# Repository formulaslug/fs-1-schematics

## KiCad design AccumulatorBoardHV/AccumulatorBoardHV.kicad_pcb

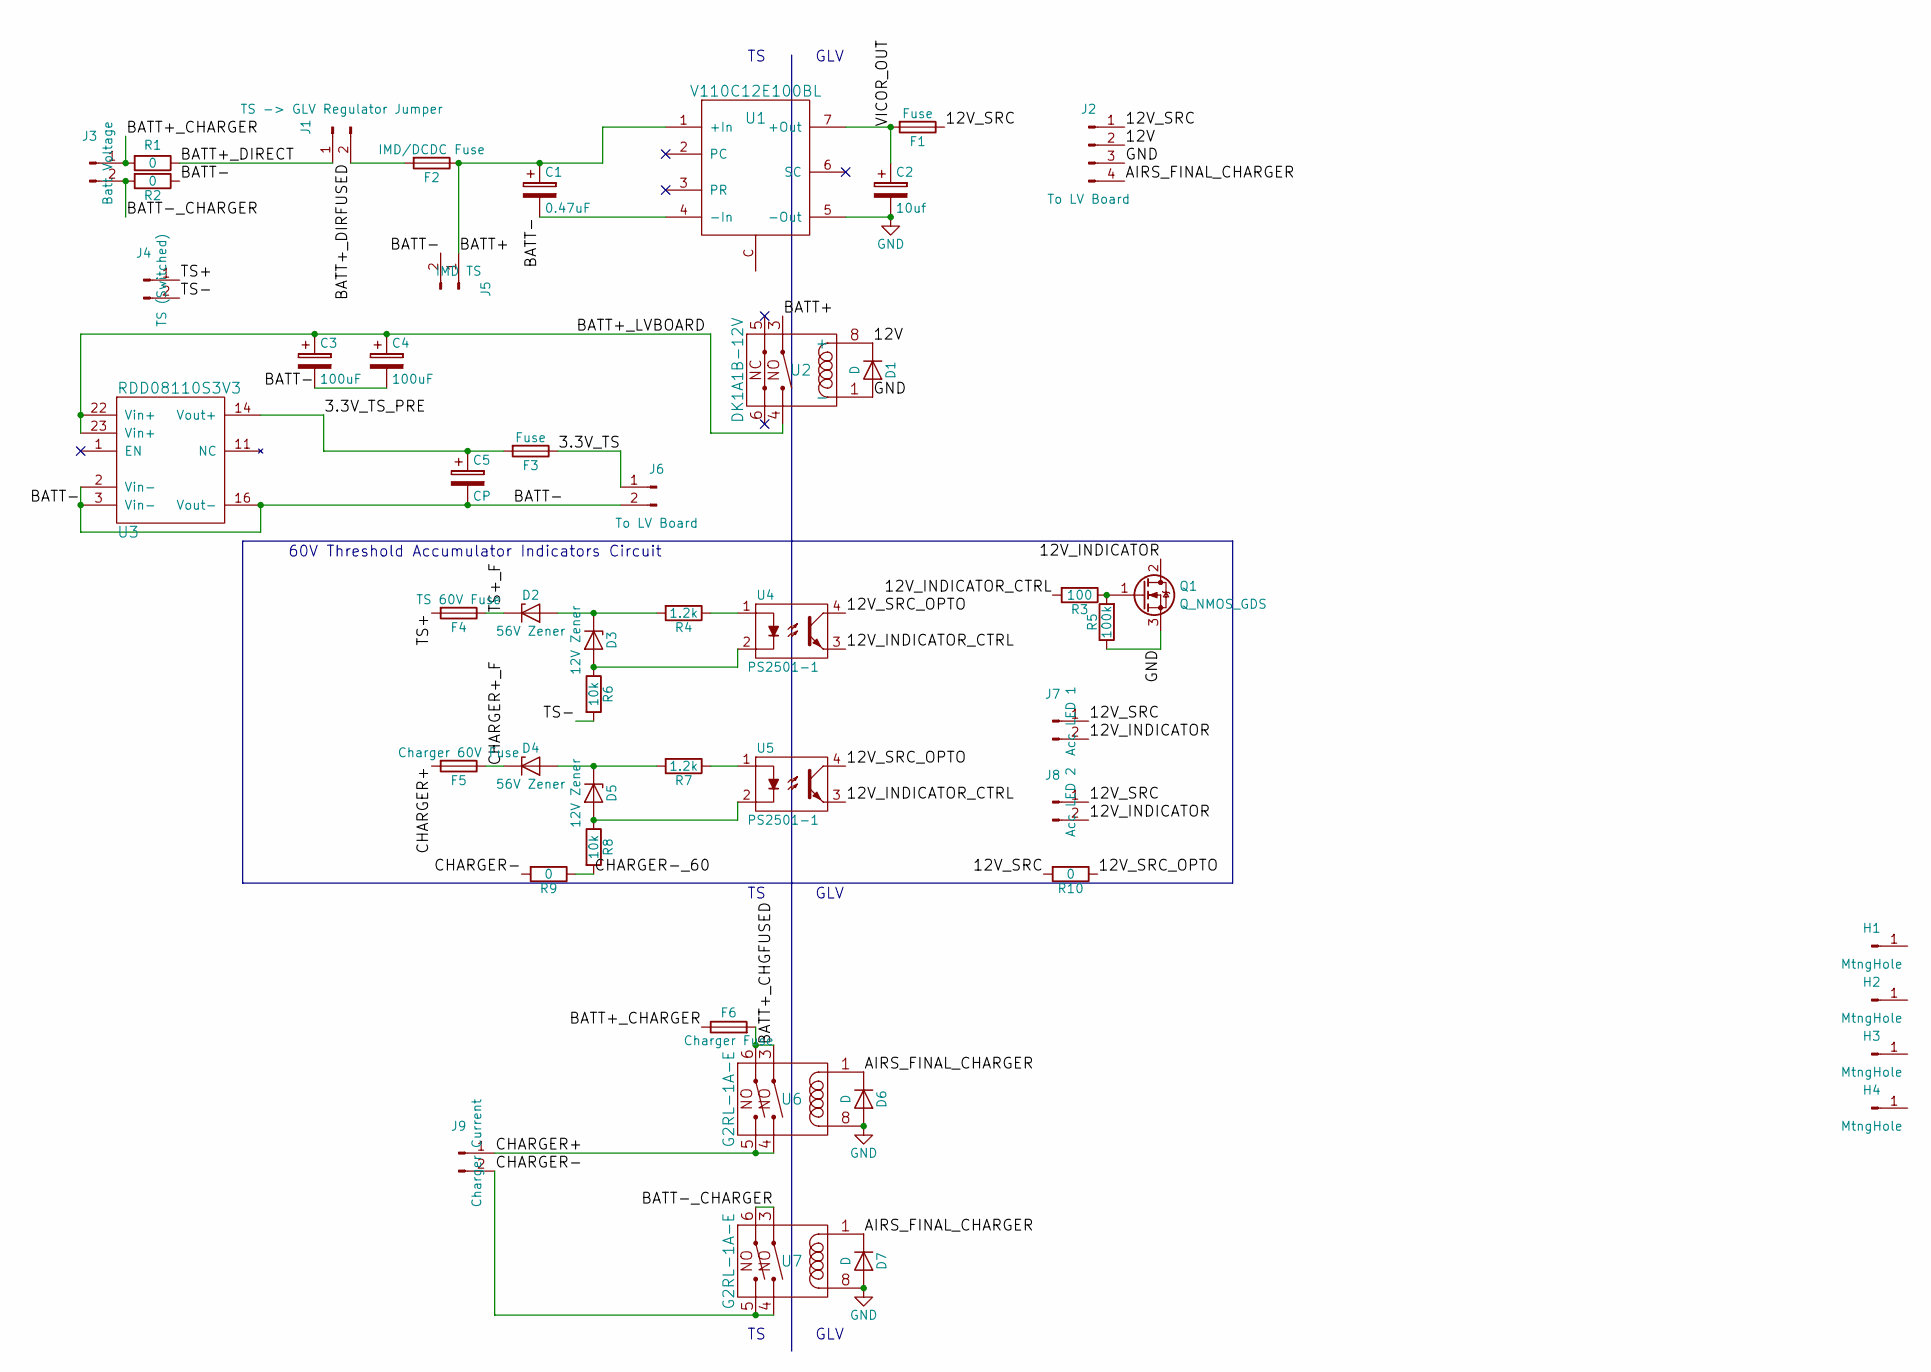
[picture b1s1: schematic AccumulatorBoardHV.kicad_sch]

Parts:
C1: 0.47uF; CP_Radial_D8.0mm_P2.50mm
C2: 10uf; CP_Radial_D8.0mm_P2.50mm
C3, C4: 100uF; CP_Radial_D16.0mm_P7.50mm
C5: CP; CP_Radial_D8.0mm_P2.50mm
D1, D6, D7: D; D_1206
D2, D4: 56V Zener; D_A-405_P7.62mm_Horizontal
D3, D5: 12V Zener; D_A-405_P7.62mm_Horizontal
F1, F3: Fuse; SMD Fuse
F2: IMD/DCDC Fuse; Fuseholder5x20_vert
F4: TS 60V Fuse; SMD Fuse
F5: Charger 60V Fuse; SMD Fuse
F6: Charger Fuse; Fuseholder5x20_vert
H1, H2, H3, H4: MtngHole; MountingHole_4.5mm
J1: TS -> GLV Regulator Jumper; Molex_NanoFit_1x02x2.50mm_Straight
J2: To LV Board; Molex_NanoFit_2x02x2.50mm_Straight
J3: Batt Voltage; Molex_MiniFit-JR-5556-02A_2x01x4.20mm_Straight
J4: TS (Switched); Molex_NanoFit_1x02x2.50mm_Straight
J5: IMD TS; Molex_NanoFit_1x02x2.50mm_Straight
J6: To LV Board; Molex_NanoFit_1x02x2.50mm_Straight
J7: Acc LED 1; Molex_NanoFit_1x02x2.50mm_Straight
J8: Acc LED 2; Molex_NanoFit_1x02x2.50mm_Straight
J9: Charger Current; Molex_MiniFit-JR-5556-02A_2x01x4.20mm_Straight
Q1: Q_NMOS_GDS; TO-220-3_Vertical
R1, R2, R9, R10: 0; SMDNetTie
R3: 100; R_Axial_DIN0207_L6.3mm_D2.5mm_P10.16mm_Horizontal
R4, R7: 1.2k; R_Axial_DIN0207_L6.3mm_D2.5mm_P10.16mm_Horizontal
R5: 100k; R_Axial_DIN0207_L6.3mm_D2.5mm_P10.16mm_Horizontal
R6, R8: 10k; R_Axial_DIN0411_L9.9mm_D3.6mm_P12.70mm_Horizontal
U1: V110C12E100BL; Vicor_Micro
U2: DK1A1B-12V
U3: RDD08110S3V3
U4, U5: PS2501-1; DIP-4_W7.62mm
U6, U7: G2RL-1A-E

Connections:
/3.3V_TS: F3.1, J6.1
/3.3V_TS_PRE: C5.1, F3.2, U3.14 (Vout+)
/12V: D1.1 (K), J2.2, U2.8 (+)
/12V_INDICATOR: J7.2, J8.2, Q1.2 (D)
/12V_INDICATOR_CTRL: R3.2, U4.3, U5.3
/12V_SRC: F1.1, J2.1, J7.1, J8.1, R10.2
/12V_SRC_OPTO: R10.1, U4.4, U5.4
/AIRS_FINAL_CHARGER: D6.1 (K), D7.1 (K), J2.4, U6.1, U7.1
/BATT+: C1.1, F2.1, J5.1, U1.1 (+In), U2.3
/BATT+_CHARGER: F6.1, J3.1, R1.2
/BATT+_CHGFUSED: F6.2, U6.3, U6.6
/BATT+_DIRECT: J1.1, R1.1
/BATT+_DIRFUSED: F2.2, J1.2
/BATT+_LVBOARD: C3.1, C4.1, U2.4, U3.22 (Vin+), U3.23 (Vin+)
/BATT-: C1.2, C3.2, C4.2, C5.2, J5.2, J6.2, R2.1, U1.4 (-In), U3.2 (Vin-), U3.3 (Vin-), U3.16 (Vout-)
/BATT-_CHARGER: J3.2, R2.2, U7.3, U7.6
/CHARGER+: F5.2, J9.1, U6.4, U6.5
/CHARGER+_F: D4.1 (K), F5.1
/CHARGER-: J9.2, R9.2, U7.4, U7.5
/CHARGER-_60: R8.2, R9.1
/TS+: F4.2, J4.1
/TS+_F: D2.1 (K), F4.1
/TS-: J4.2, R6.2
/VICOR_OUT: C2.1, F1.2, U1.7 (+Out)
GND: C2.2, D1.2 (A), D6.2 (A), D7.2 (A), J2.3, Q1.3 (S), R5.1, U1.5 (-Out), U2.1 (-), U6.8, U7.8
unnamed: D2.2 (A), D3.1 (K), R4.2
unnamed: D3.2 (A), R6.1, U4.2
unnamed: D4.2 (A), D5.1 (K), R7.2
unnamed: D5.2 (A), R8.1, U5.2
unnamed: Q1.1 (G), R3.1, R5.2
unnamed: R4.1, U4.1
unnamed: R7.1, U5.1

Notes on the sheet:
TS GLV
60V Threshold Accumulator Indicators Circuit

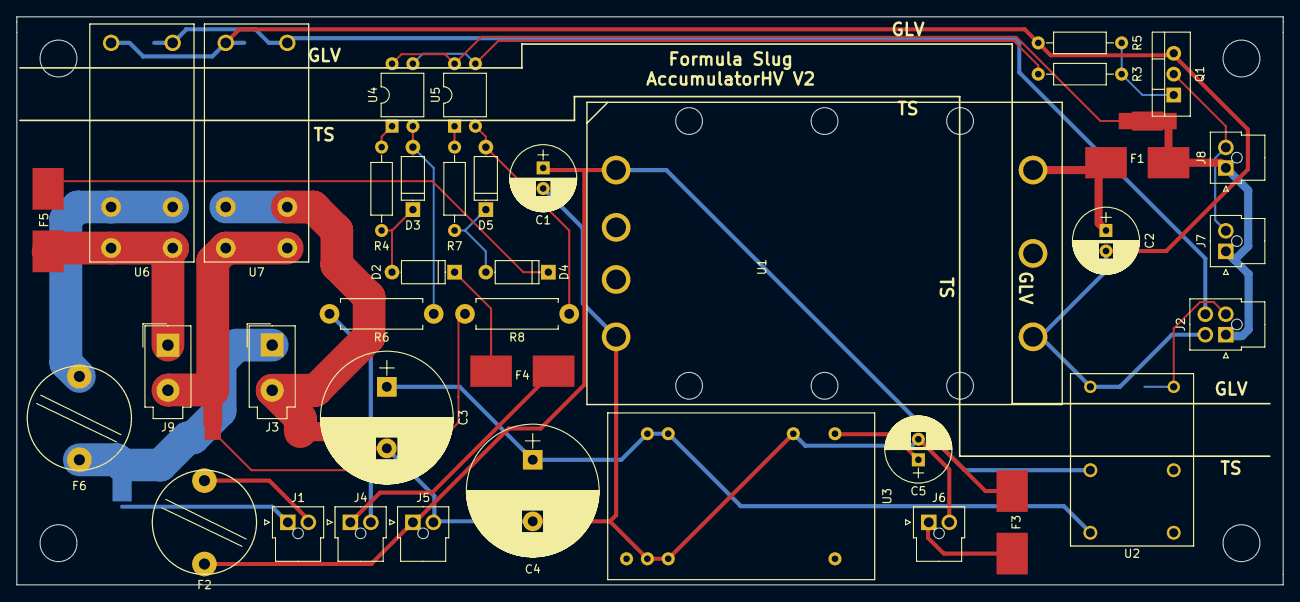
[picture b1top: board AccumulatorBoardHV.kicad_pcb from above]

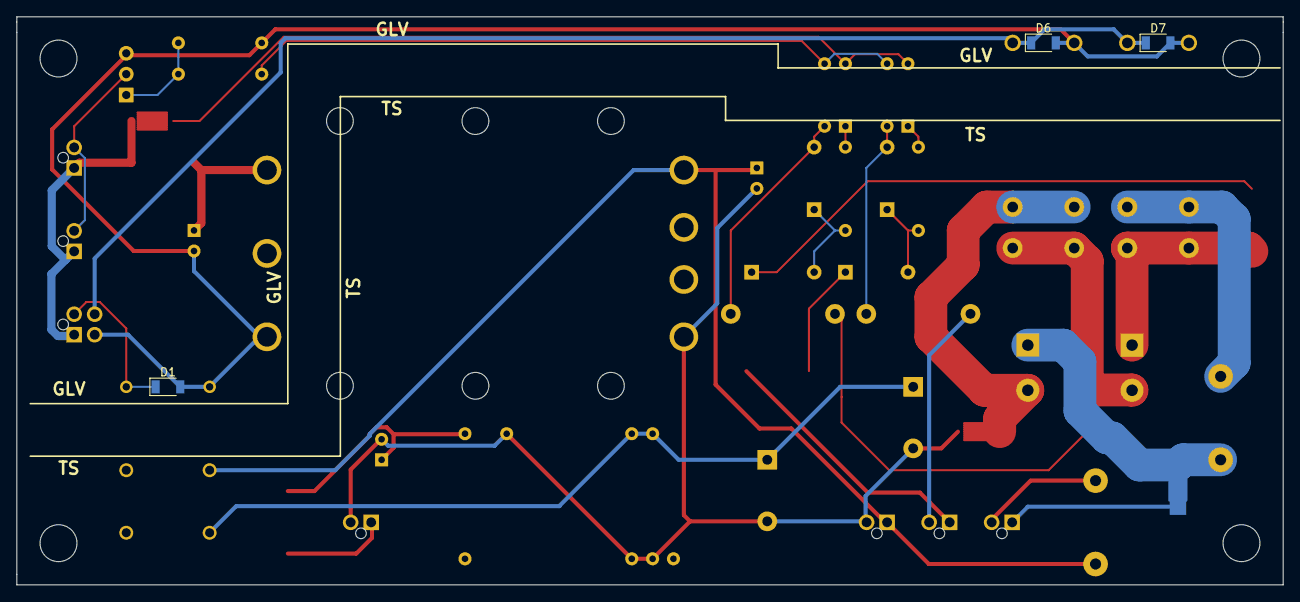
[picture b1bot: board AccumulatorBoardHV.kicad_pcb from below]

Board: 2 copper layers, 154.3 x 69.2 mm, 49 parts (4 on the bottom side), 32 nets.

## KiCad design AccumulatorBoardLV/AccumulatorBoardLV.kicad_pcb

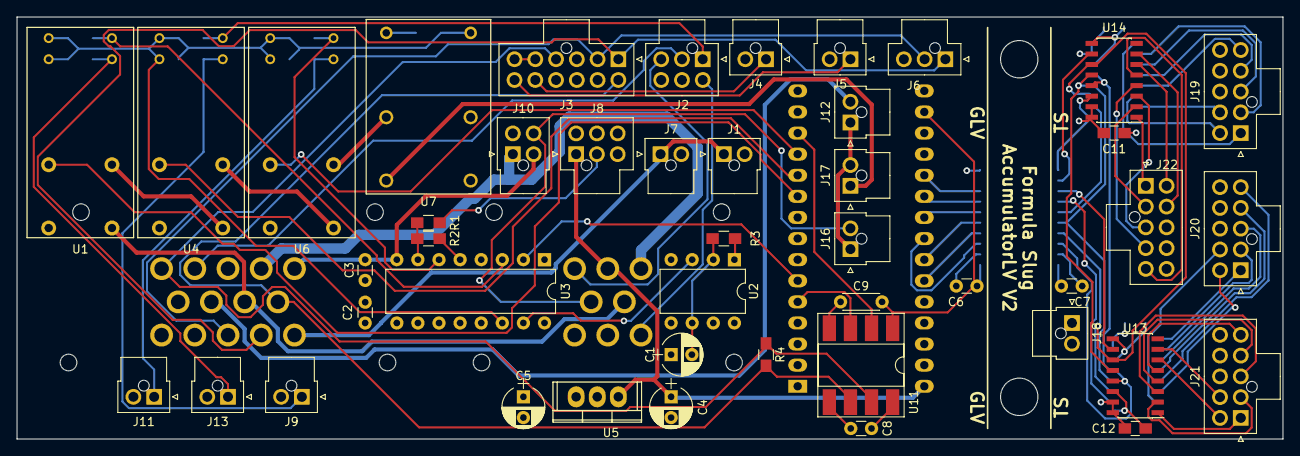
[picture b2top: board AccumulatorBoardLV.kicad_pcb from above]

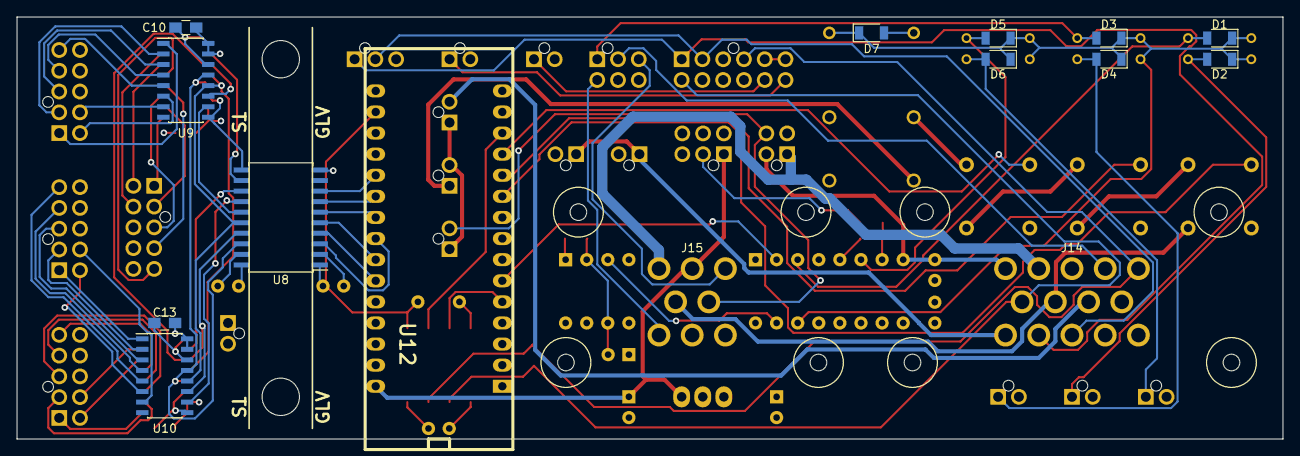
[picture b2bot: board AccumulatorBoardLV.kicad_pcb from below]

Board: 4 copper layers, 152.4 x 50.8 mm, 62 parts (15 on the bottom side), 84 nets.

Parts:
C1, C4, C5: 10uF; CP_Radial_D5.0mm_P2.50mm
C2, C3, C6, C7: 0.1uF; C_Disc_D3.0mm_W1.6mm_P2.50mm
C8: CP; C_Disc_D3.0mm_W1.6mm_P2.50mm
C9: CP; C_Disc_D4.3mm_W1.9mm_P5.00mm
C10, C11, C12, C13: 1uF; C_0805_HandSoldering
D1, D2, D3, D4, D5, D6, D7: D; D_1206
H1, H2: MtngHole; MountingHole_4.5mm
J1: Contactor 1; Molex_NanoFit_1x02x2.50mm_Straight
J2: BMS Connector 1; Molex_NanoFit_2x03x2.50mm_Straight
J3: BMS Connector 2; Molex_NanoFit_2x06x2.50mm_Straight
J4: BMS TX; Molex_NanoFit_1x02x2.50mm_Straight
J5: BMS RX; Molex_NanoFit_1x02x2.50mm_Straight
J6: Current Sensor; Molex_NanoFit_1x03x2.50mm_Straight
J7: Contactor 2; Molex_NanoFit_1x02x2.50mm_Straight
J8: IMD LV; Molex_NanoFit_2x03x2.50mm_Straight
J9: BMS Reset; Molex_NanoFit_1x02x2.50mm_Straight
J10: To HV Board; Molex_NanoFit_2x02x2.50mm_Straight
J11: IMD Reset; Molex_NanoFit_1x02x2.50mm_Straight
J12: TS Interlock; Molex_NanoFit_1x02x2.50mm_Straight
J13: Temp Reset; Molex_NanoFit_1x02x2.50mm_Straight
J14: To ECU; Ampseal-776261
J15: Charger LV; Ampseal-776276-1
J16: Charger Interlock; Molex_NanoFit_1x02x2.50mm_Straight
J17: Lid Interlock; Molex_NanoFit_1x02x2.50mm_Straight
J18: From HV Board; Molex_NanoFit_1x02x2.50mm_Straight
J19: Chip 1; Molex_NanoFit_2x05x2.50mm_Straight
J20: Chip 2; Molex_NanoFit_2x05x2.50mm_Straight
J21: Chip 3; Molex_NanoFit_2x05x2.50mm_Straight
J22: Chip 4; Molex_NanoFit_2x05x2.50mm_Straight
R1, R2: 1.1kR; R_0805_HandSoldering
R3: 470kR; R_0805_HandSoldering
R4: 120; R_0805_HandSoldering
U1, U4, U6: DE1A1B-L2-12V
U2: LM555N; DIP-8_W7.62mm
U3: SN754410; DIP-16_W7.62mm
U5: L78S05CV-DG; TO-220
U7: DK1A1B-12V
U8: ADUM4154ARIZ; SOIC-20W_7.5x12.8mm_Pitch1.27mm
U9, U10, U13, U14: MCP3008; SOIC-16_3.9x9.9mm_Pitch1.27mm
U11: ISO1050; DIP-8_W8.89mm_SMDSocket_LongPads
U12: stm_nucleo_FK303K8; arduino_mini

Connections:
+3V3: C6.1, C9.1, U8.1, U11.1, U12.17
+5V: C1.1, C2.1, C5.1, C8.1, U2.4, U2.8, U3.1, U3.9, U3.16, U5.3, U11.8
+12V: C3.1, C4.1, J8.1, J10.2, J14.1, J15.2, U3.8, U5.1, U12.30
/3.3V_TS: C7.1, C10.1, C11.1, C12.1, C13.1, J18.1, J19.9, J20.9, J21.9, J22.9, U8.20, U9.15, U9.16, U10.15, U10.16, U13.15, U13.16, U14.15, U14.16
/5V_BMS: J3.1, J6.1, J14.11
/12V_SRC: J10.1, J14.2, J15.1
/AIRS_ACC_OUT: J12.2, J14.8
/AIRS_BMS_OUT: U4.6, U6.5
/AIRS_CHARGER_OUT: J14.7, J15.4, U1.5
/AIRS_FINAL: J1.1, J7.1, J14.10
/AIRS_FINAL_CHARGER: J10.4, J15.5, J16.2
/AIRS_IMD_OUT: U6.6, U7.3
/AIRS_LID_OUT: J12.1, J16.1, J17.2
/AIRS_RELAYS_OUT: J17.1, U7.4
/AIRS_TEMP_OUT: U1.6, U4.5
/BATT-: C7.2, C10.2, C11.2, C12.2, C13.2, J18.2, J19.10, J20.10, J21.10, J22.10, U8.11, U8.19, U9.9, U9.14, U10.9, U10.14, U13.9, U13.14, U14.9, U14.14
/BMS_FLT: D3.2, J2.1, U4.8
/BMS_FLT_LATCHED: U4.3, U12.11
/BMS_RESET: D4.2, J9.1, U4.7
/BMS_RX: J3.12, J5.1
/BMS_TX: J3.11, J4.1
/CAN_H: J3.4, J14.5, R4.1, U11.7
/CAN_L: J3.7, J14.6, R4.2, U11.6
/CAN_RX: U11.2, U12.13
/CAN_TX: U11.3, U12.5
/CHARGER_CONTROL: J2.4, J15.6
/IMD_FLT: J8.2, R1.2
/IMD_FLT_5: R1.1, R2.1, U3.7
/IMD_FLT_H: D5.2, U3.6, U6.8
/IMD_FLT_LATCHED: U6.3, U12.12
/IMD_RESET: D6.2, J11.1, U6.7
/SCLK: U8.18, U9.13, U10.13, U13.13, U14.13
/SIG_CURRENT: J3.2, J6.2, J14.12
/TEMP_FLT: U3.2, U12.6
/TEMP_FLT_H: D1.2, U1.8, U3.3
/TEMP_FLT_LATCHED: U1.3, U12.10
/TEMP_RESET: D2.2, J13.1, U1.7
/TEMP_SSI: U8.17, U9.11, U10.11, U13.11, U14.11
/TEMP_SSO: U8.16, U9.12, U10.12, U13.12, U14.12
/TEMP_SS_0: U8.15, U9.10
/TEMP_SS_1: U8.14, U10.10
/TEMP_SS_2: U8.13, U13.10
/TEMP_SS_3: U8.12, U14.10
/TIMER: U2.3, U3.15
/TIMER_H: D1.1, D2.1, D3.1, D4.1, D5.1, D6.1, D7.1, U1.1, U1.2, U3.14, U4.1, U4.2, U6.1, U6.2, U7.8
/V_L: J2.2, J14.4
/V_S: J2.3, J15.3
GND: C2.2, C3.2, C4.2, C5.2, C6.2, C8.2, C9.2, D7.2, J1.2, J2.5, J3.3, J3.8, J3.9, J3.10, J4.2, J5.2, J6.3, J7.2, J8.3, J8.4, J8.5, J9.2, J10.3, J11.2, J13.2, J14.3, J15.8, R2.2, R3.2, U1.4, U2.1, U3.4, U3.5, U3.12, U3.13, U4.4, U5.2, U6.4, U7.1, U8.2, U8.10, U11.4, U11.5, U12.4, U12.29
unnamed: C1.2, R3.1, U2.2, U2.6
unnamed: J3.5, J3.6
unnamed: J19.1, U9.1
unnamed: J19.2, U9.2
unnamed: J19.3, U9.3
unnamed: J19.4, U9.4
unnamed: J19.5, U9.5
unnamed: J19.6, U9.6
unnamed: J19.7, U9.7
unnamed: J20.1, U10.1
unnamed: J20.2, U10.2
unnamed: J20.3, U10.3
unnamed: J20.4, U10.4
unnamed: J20.5, U10.5
unnamed: J20.6, U10.6
unnamed: J20.7, U10.7
unnamed: J21.1, U13.1
unnamed: J21.2, U13.2
unnamed: J21.3, U13.3
unnamed: J21.4, U13.4
unnamed: J21.5, U13.5
unnamed: J21.6, U13.6
unnamed: J21.7, U13.7
unnamed: J22.1, U14.1
unnamed: J22.2, U14.2
unnamed: J22.3, U14.3
unnamed: J22.4, U14.4
unnamed: J22.5, U14.5
unnamed: J22.6, U14.6
unnamed: J22.7, U14.7
unnamed: U8.8, U12.20
unnamed: U8.7, U12.21
unnamed: U8.6, U12.22
unnamed: U8.3, U12.23
unnamed: U8.5, U12.24
unnamed: U8.4, U12.25

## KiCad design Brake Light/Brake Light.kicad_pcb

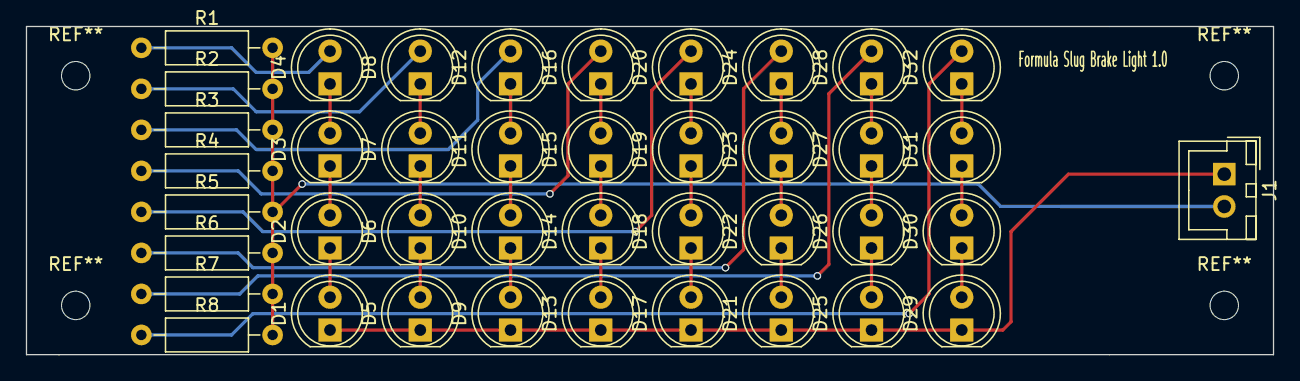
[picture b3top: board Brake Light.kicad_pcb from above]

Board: 2 copper layers, 96.5 x 25.4 mm, 41 parts (0 on the bottom side), 34 nets.

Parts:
D1, D2, D3, D4, D5, D6, D7, D8, D9, D10, D11, D12, D13, D14, D15, D16, D17, D18, D19, D20, D21, D22, D23, D24, D25, D26, D27, D28, D29, D30, D31, D32: LED_Small; LED_D5.0mm
J1: CONN_01X04; JST_XH_B02B-XH-A_02x2.50mm_Straight
R1, R2, R3, R4, R5, R6, R7, R8: 180; R_Axial_DIN0207_L6.3mm_D2.5mm_P10.16mm_Horizontal

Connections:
+12V: D1.1, D5.1, D9.1, D13.1, D17.1, D21.1, D25.1, D29.1, J1.1
GND: J1.2, R1.2, R2.2, R3.2, R4.2, R5.2, R6.2, R7.2, R8.2
unnamed: D1.2, D2.1
unnamed: D2.2, D3.1
unnamed: D3.2, D4.1
unnamed: D4.2, R1.1
unnamed: D5.2, D6.1
unnamed: D6.2, D7.1
unnamed: D7.2, D8.1
unnamed: D8.2, R2.1
unnamed: D9.2, D10.1
unnamed: D10.2, D11.1
unnamed: D11.2, D12.1
unnamed: D12.2, R3.1
unnamed: D13.2, D14.1
unnamed: D14.2, D15.1
unnamed: D15.2, D16.1
unnamed: D16.2, R4.1
unnamed: D17.2, D18.1
unnamed: D18.2, D19.1
unnamed: D19.2, D20.1
unnamed: D20.2, R5.1
unnamed: D21.2, D22.1
unnamed: D22.2, D23.1
unnamed: D23.2, D24.1
unnamed: D24.2, R6.1
unnamed: D25.2, D26.1
unnamed: D26.2, D27.1
unnamed: D27.2, D28.1
unnamed: D28.2, R7.1
unnamed: D29.2, D30.1
unnamed: D30.2, D31.1
unnamed: D31.2, D32.1
unnamed: D32.2, R8.1

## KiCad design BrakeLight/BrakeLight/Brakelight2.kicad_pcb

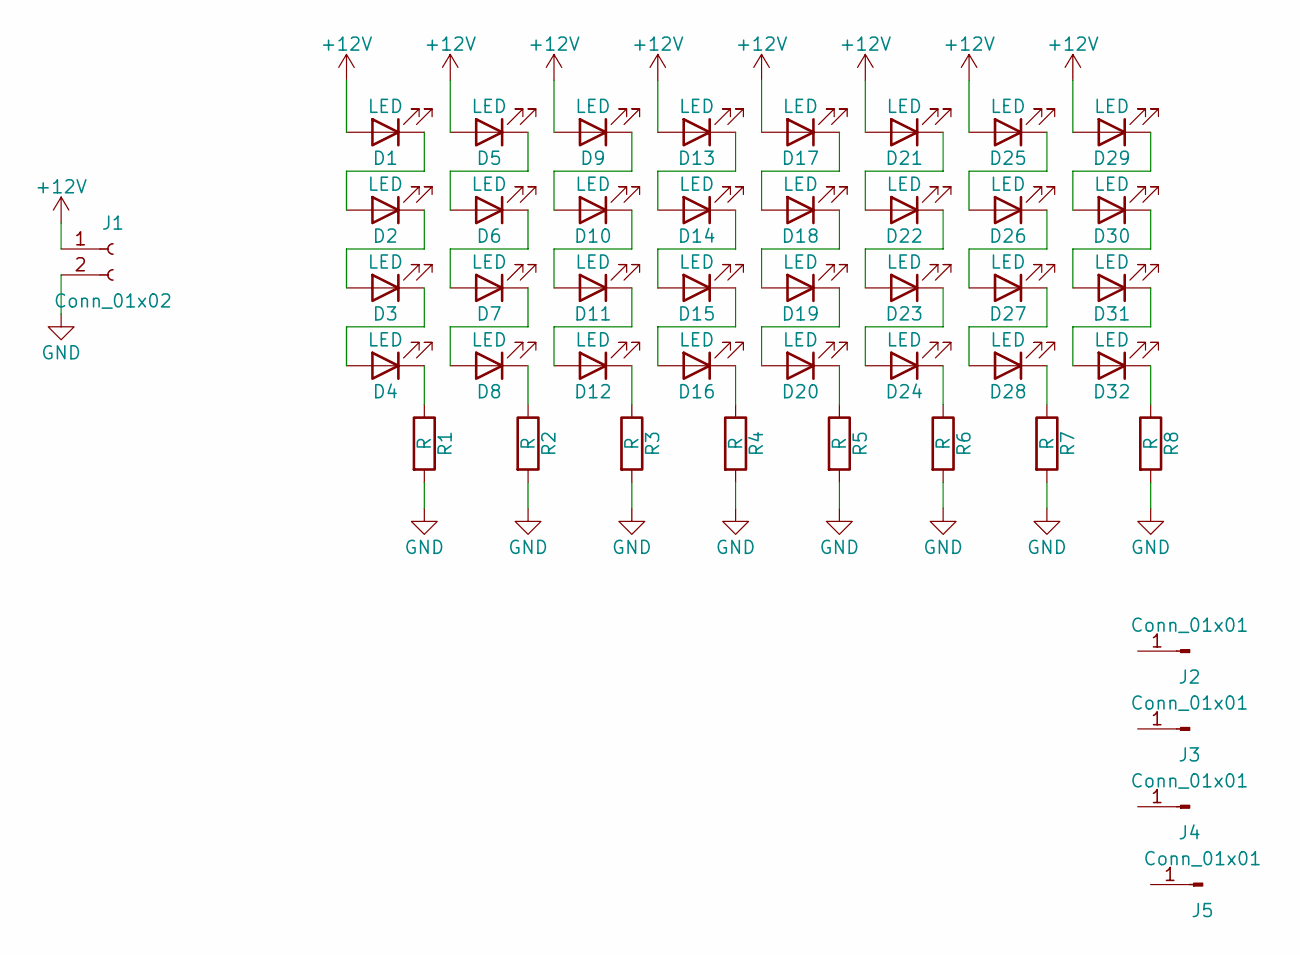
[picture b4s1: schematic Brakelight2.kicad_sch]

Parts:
D1, D2, D3, D4, D5, D6, D7, D8, D9, D10, D11, D12, D13, D14, D15, D16, D17, D18, D19, D20, D21, D22, D23, D24, D25, D26, D27, D28, D29, D30, D31, D32: LED; LED_D5.0mm
J1: Conn_01x02; Molex_NanoFit_1x02x2.50mm_Straight
J2, J3, J4, J5: Conn_01x01; MountingHole_3.2mm_M3
R1, R2, R3, R4, R5, R6, R7, R8: R; R_Axial_DIN0207_L6.3mm_D2.5mm_P10.16mm_Horizontal

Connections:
+12V: D1.2 (A), D5.2 (A), D9.2 (A), D13.2 (A), D17.2 (A), D21.2 (A), D25.2 (A), D29.2 (A), J1.1
GND: J1.2, R1.2, R2.2, R3.2, R4.2, R5.2, R6.2, R7.2, R8.2
unnamed: D1.1 (K), D2.2 (A)
unnamed: D2.1 (K), D3.2 (A)
unnamed: D3.1 (K), D4.2 (A)
unnamed: D4.1 (K), R1.1
unnamed: D5.1 (K), D6.2 (A)
unnamed: D6.1 (K), D7.2 (A)
unnamed: D7.1 (K), D8.2 (A)
unnamed: D8.1 (K), R2.1
unnamed: D10.1 (K), D11.2 (A)
unnamed: D9.1 (K), D10.2 (A)
unnamed: D11.1 (K), D12.2 (A)
unnamed: D12.1 (K), R3.1
unnamed: D13.1 (K), D14.2 (A)
unnamed: D14.1 (K), D15.2 (A)
unnamed: D15.1 (K), D16.2 (A)
unnamed: D16.1 (K), R4.1
unnamed: D17.1 (K), D18.2 (A)
unnamed: D18.1 (K), D19.2 (A)
unnamed: D19.1 (K), D20.2 (A)
unnamed: D20.1 (K), R5.1
unnamed: D21.1 (K), D22.2 (A)
unnamed: D22.1 (K), D23.2 (A)
unnamed: D23.1 (K), D24.2 (A)
unnamed: D24.1 (K), R6.1
unnamed: D25.1 (K), D26.2 (A)
unnamed: D26.1 (K), D27.2 (A)
unnamed: D27.1 (K), D28.2 (A)
unnamed: D28.1 (K), R7.1
unnamed: D29.1 (K), D30.2 (A)
unnamed: D30.1 (K), D31.2 (A)
unnamed: D31.1 (K), D32.2 (A)
unnamed: D32.1 (K), R8.1

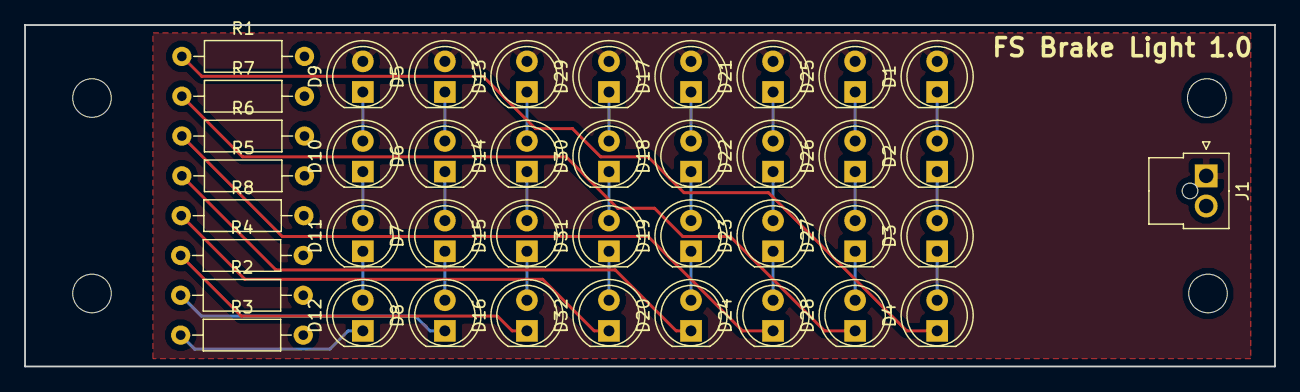
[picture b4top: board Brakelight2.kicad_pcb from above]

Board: 2 copper layers, 103.6 x 28.3 mm, 45 parts (0 on the bottom side), 34 nets.

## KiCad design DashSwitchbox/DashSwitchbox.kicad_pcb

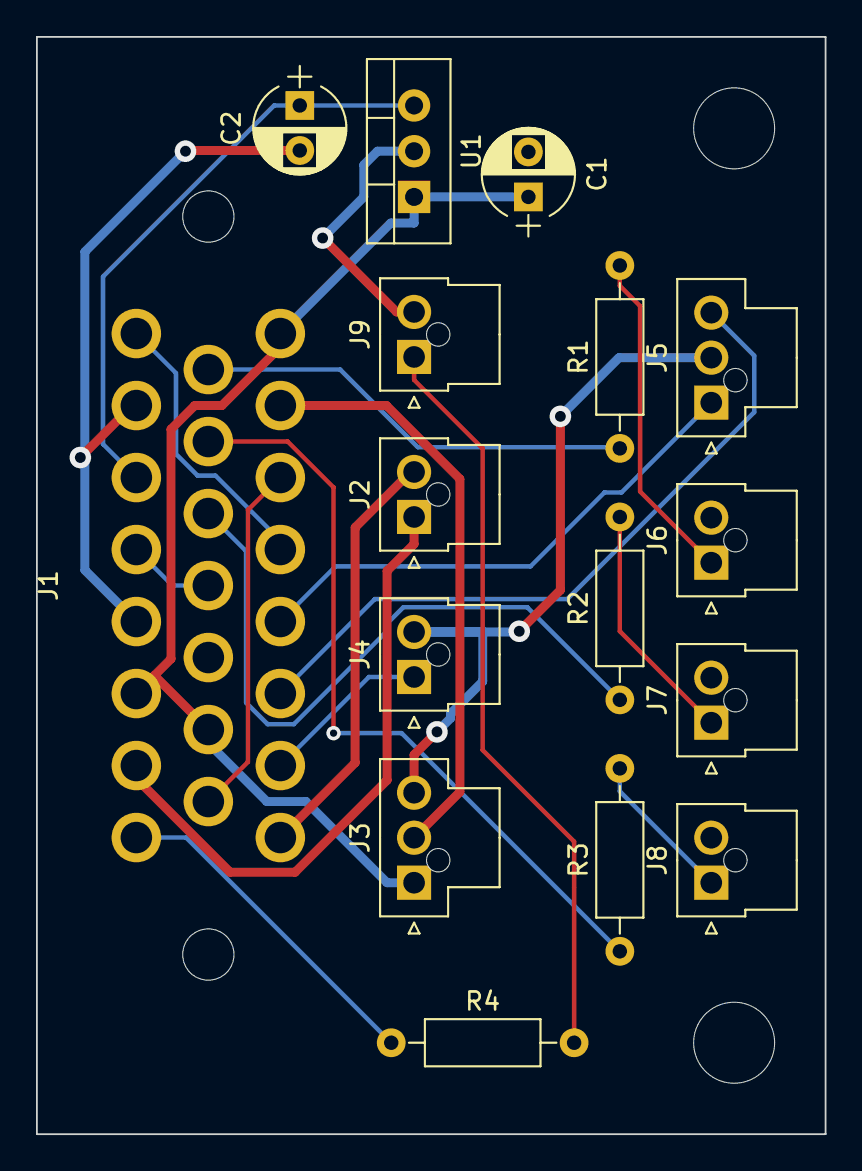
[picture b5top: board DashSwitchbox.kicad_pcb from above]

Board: 2 copper layers, 43.8 x 61.0 mm, 18 parts (0 on the bottom side), 20 nets.

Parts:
C1, C2: CP; CP_Radial_D5.0mm_P2.50mm
H1, H2: MtngHole; MountingHole_4.5mm
J1: Main Connector; Ampseal23
J2: Estop Connector; Molex_NanoFit_1x02x2.50mm_Straight
J3: Dash LVMS; Molex_NanoFit_1x03x2.50mm_Straight
J4: To Drive Mode Button; Molex_NanoFit_1x02x2.50mm_Straight
J5: To Drive Mode Switch; Molex_NanoFit_1x03x2.50mm_Straight
J6: AMS Fault LED; Molex_NanoFit_1x02x2.50mm_Straight
J7: BSPD Fault LED; Molex_NanoFit_1x02x2.50mm_Straight
J8: IMD Fault LED; Molex_NanoFit_1x02x2.50mm_Straight
J9: Inertia Fault LED; Molex_NanoFit_1x02x2.50mm_Straight
R1, R2, R3: 51; R_Axial_DIN0207_L6.3mm_D2.5mm_P10.16mm_Horizontal
R4: 390; R_Axial_DIN0207_L6.3mm_D2.5mm_P10.16mm_Horizontal
U1: LD1117V33; TO-220-3_Vertical

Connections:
+3V3: C2.1, J1.18, U1.3
+12V: C1.1, J1.1, J1.14, J1.21, J3.1, U1.1
/12V_LVMS: J1.2, J3.2
/AIRS_DASH_OUT: J1.8, J2.2
/AIRS_INERTIA_OUT: J1.22, J2.1
/BUTTON_1: J1.5, J5.1
/BUTTON_2: J1.6, J5.3
/BUTTON_3: J1.7, J4.1
/CAN_H: J1.3, J1.15
/CAN_L: J1.4, J1.16
/FLT_INERTIA: J1.23, R4.1
/LED_AMS: J1.9, R1.1
/LED_BSPD: J1.11, R2.1
/LED_IMD: J1.10, R3.1
/SIG_STEER: J1.12, J1.19
GND: C1.2, C2.2, J1.13, J1.17, J1.20, J3.3, J4.2, J5.2, J6.2, J7.2, J8.2, J9.2, U1.2
unnamed: J6.1, R1.2
unnamed: J7.1, R2.2
unnamed: J8.1, R3.2
unnamed: J9.1, R4.2

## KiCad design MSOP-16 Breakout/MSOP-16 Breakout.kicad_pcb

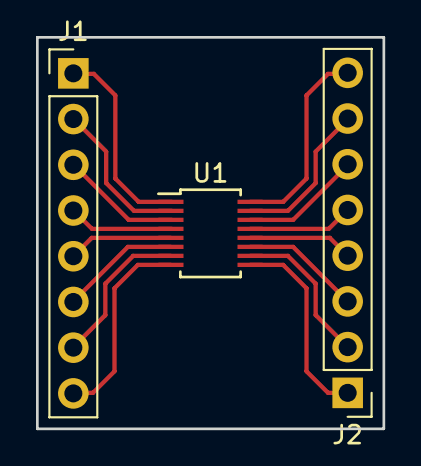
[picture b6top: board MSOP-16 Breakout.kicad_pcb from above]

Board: 2 copper layers, 19.3 x 21.7 mm, 3 parts (0 on the bottom side), 16 nets.

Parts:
J1, J2: Conn_01x08_Male; PinHeader_1x08_P2.54mm_Vertical
U1: LTC6820; MSOP-16_[LTC6820]_10_thou_compat

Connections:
1: J1.1, U1.1
2: J1.2, U1.2
3: J1.3, U1.3
4: J1.4, U1.4
5: J1.5, U1.5
6: J1.6, U1.6
7: J1.7, U1.7
8: J1.8, U1.8
9: J2.1, U1.9
10: J2.2, U1.10
11: J2.3, U1.11
12: J2.4, U1.12
13: J2.5, U1.13
14: J2.6, U1.14
15: J2.7, U1.15
16: J2.8, U1.16
